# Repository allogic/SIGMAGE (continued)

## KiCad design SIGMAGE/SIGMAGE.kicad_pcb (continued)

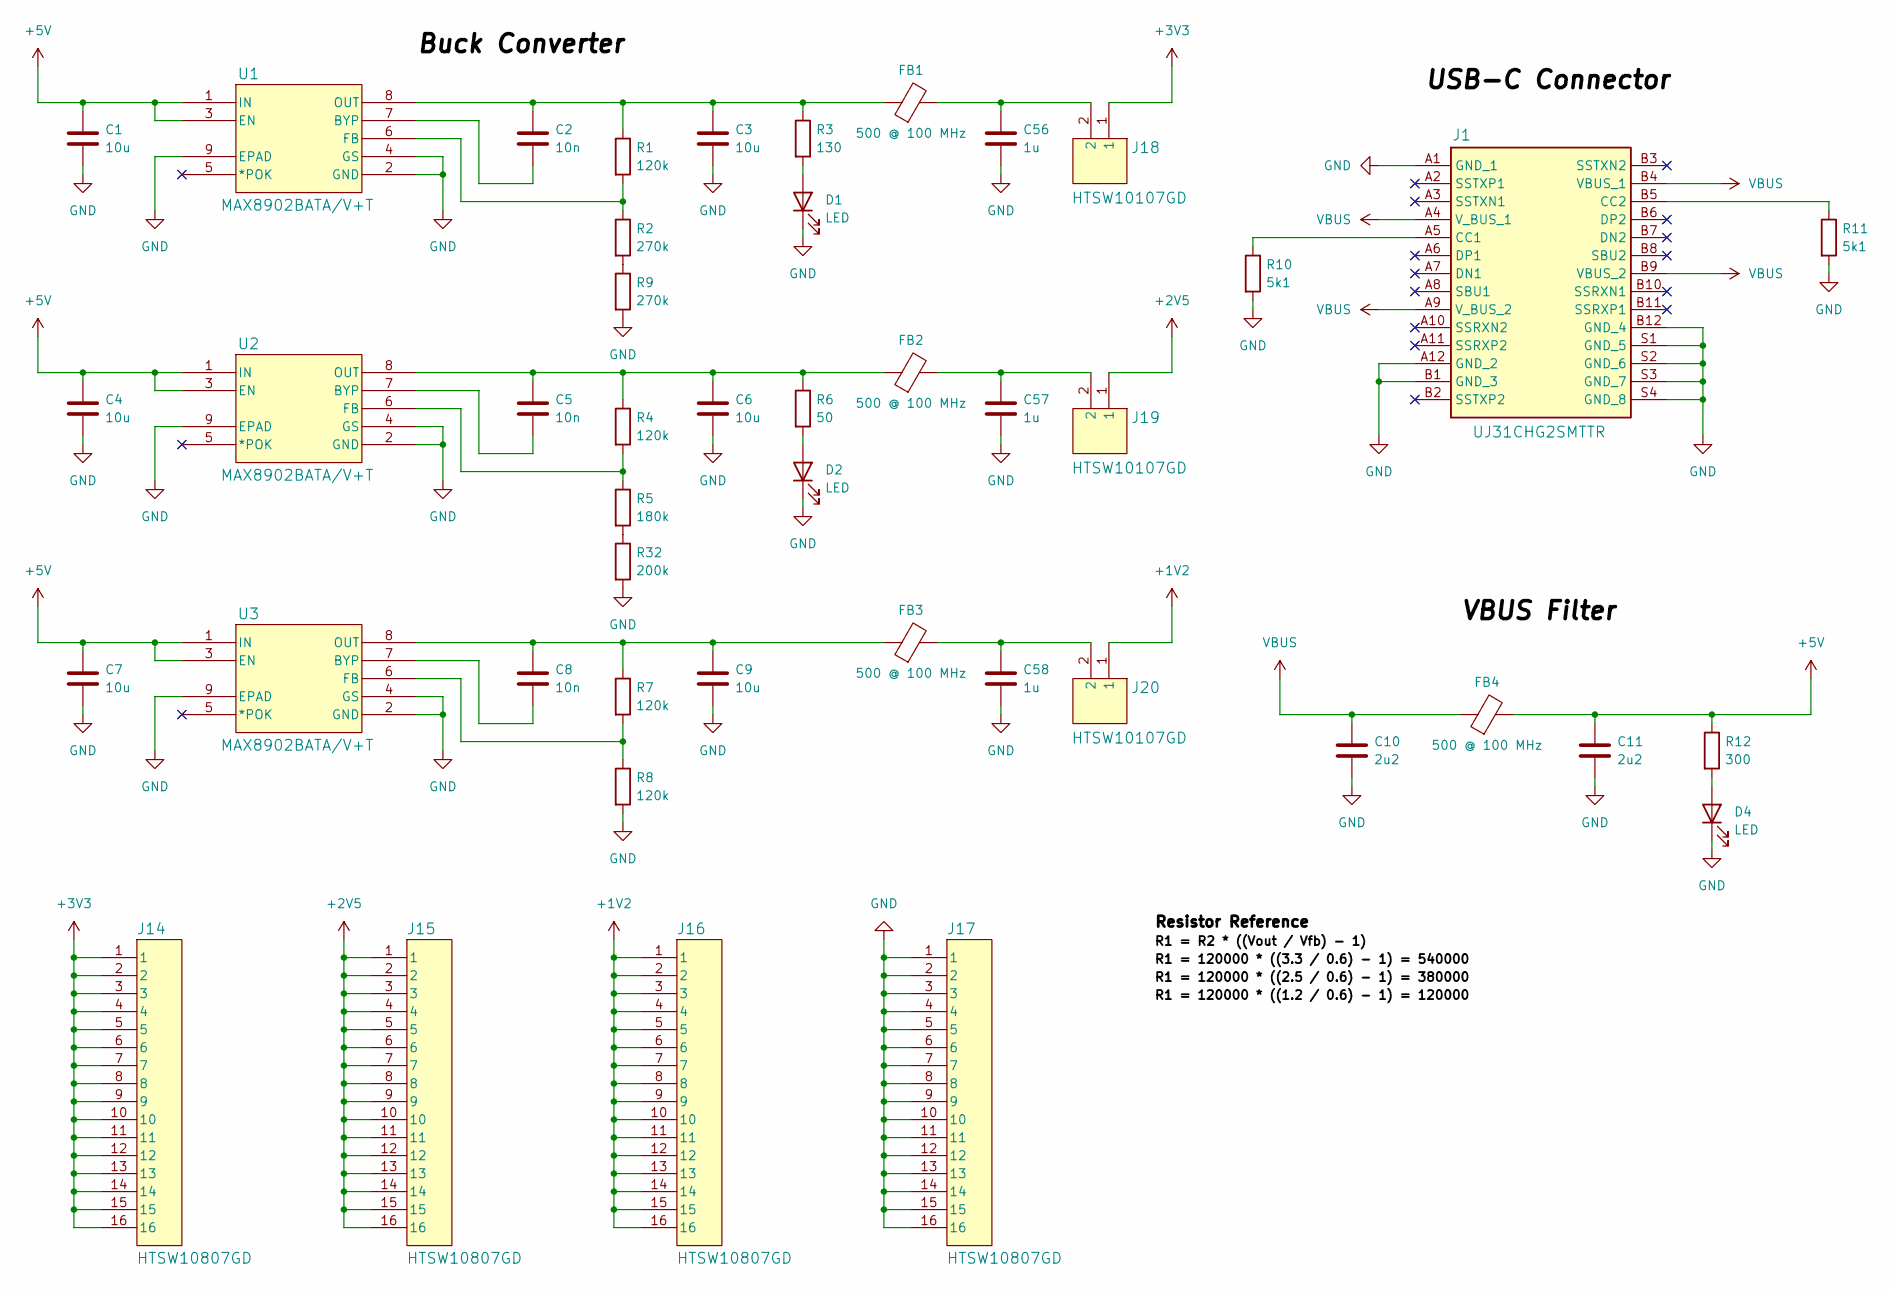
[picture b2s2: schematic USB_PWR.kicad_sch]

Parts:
C1, C3, C4, C6, C7, C9: 10u; C_0603_1608Metric
C2, C5, C8: 10n; C_0603_1608Metric
C10, C11: 2u2; C_0603_1608Metric
C56, C57, C58: 1u; C_0603_1608Metric
D1, D2, D4: LED; LED_0603_1608Metric
FB1, FB2, FB3, FB4: 500 @ 100 MHz; C_0603_1608Metric
J1: UJ31CHG2SMTTR; Manufacturer_Part_Number UJ31-CH-G2-SMT-TR; Mouser Part Number 490-UJ31-CH-G2SMT-TR
J14, J15, J16, J17: HTSW10807GD
J18, J19, J20: HTSW10107GD
R1, R4, R7, R8: 120k; R_0603_1608Metric
R2, R9: 270k; R_0603_1608Metric
R3: 130; R_0603_1608Metric
R5: 180k; R_0603_1608Metric
R6: 50; R_0603_1608Metric
R10, R11: 5k1; R_0603_1608Metric
R12: 300; R_0603_1608Metric
R32: 200k; R_0603_1608Metric
U1, U2, U3: MAX8902BATA/V+T; MAX8902BATAVT

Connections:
GND: C1.2, C3.2, C4.2, C6.2, C7.2, C9.2, C10.2, C11.2, C56.2, C57.2, C58.2, D1.1 (K), D2.1 (K), D4.1 (K), J1.A1 (GND_1), J1.A12 (GND_2), J1.B1 (GND_3), J1.B12 (GND_4), J1.S1 (GND_5), J1.S2 (GND_6), J1.S3 (GND_7), J1.S4 (GND_8), J17.1, J17.2, J17.3, J17.4, J17.5, J17.6, J17.7, J17.8, J17.9, J17.10, J17.11, J17.12, J17.13, J17.14, J17.15, J17.16, R8.2, R9.2, R10.2, R11.2, R32.2, U1.2 (GND), U1.4 (GS), U1.9 (EPAD), U2.2 (GND), U2.4 (GS), U2.9 (EPAD), U3.2 (GND), U3.4 (GS), U3.9 (EPAD); also elsewhere on the board
unnamed: C8.1, C9.1, FB3.1, R7.1, U3.8 (OUT)
unnamed: C8.2, U3.7 (BYP)
unnamed: C56.1, FB1.2, J18.2
unnamed: C57.1, FB2.2, J19.2
unnamed: C58.1, FB3.2, J20.2
unnamed: D1.2 (A), R3.2
unnamed: D2.2 (A), R6.2
unnamed: D4.2 (A), R12.2
unnamed: J1.A5 (CC1), R10.1
unnamed: J1.B5 (CC2), R11.1
unnamed: R2.2, R9.1
unnamed: R7.2, R8.1, U3.6 (FB)
unnamed: R5.2, R32.1
unnamed: C2.2, U1.7 (BYP)
unnamed: R1.2, R2.1, U1.6 (FB)
unnamed: C2.1, C3.1, FB1.1, R1.1, R3.1, U1.8 (OUT)
unnamed: C5.2, U2.7 (BYP)
unnamed: R4.2, R5.1, U2.6 (FB)
unnamed: C5.1, C6.1, FB2.1, R4.1, R6.1, U2.8 (OUT)
VBUS: C10.1, FB4.1, J1.A4 (V_BUS_1), J1.A9 (V_BUS_2), J1.B4 (VBUS_1), J1.B9 (VBUS_2)

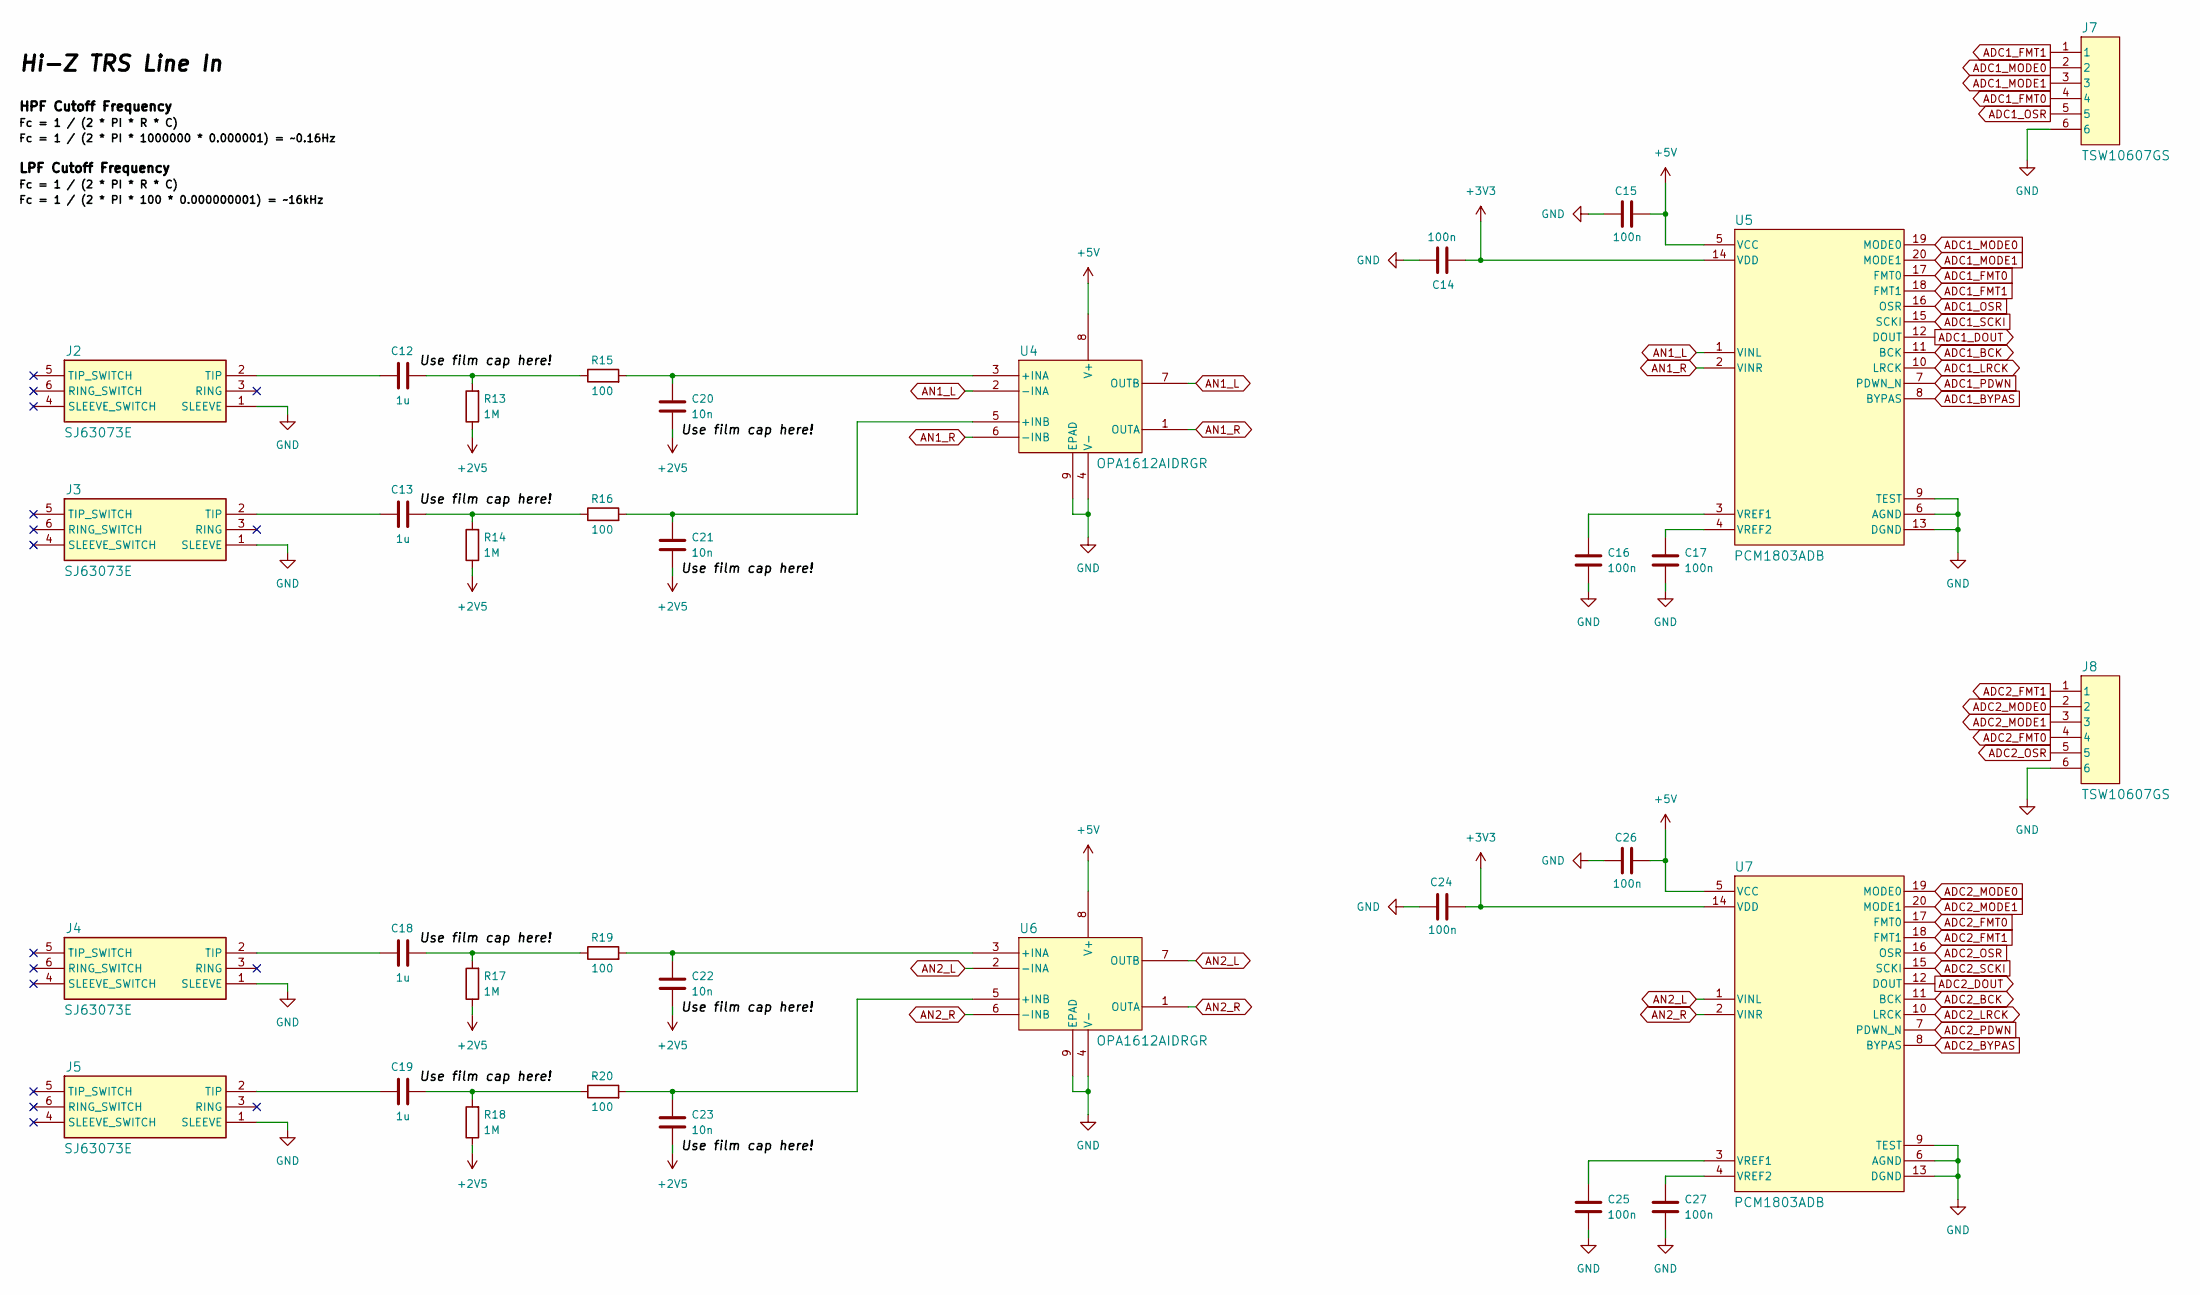
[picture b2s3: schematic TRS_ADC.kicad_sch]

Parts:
C12, C13, C18, C19: 1u; C_1206_3216Metric
C14, C15, C16, C17, C24, C25, C26, C27: 100n; C_0603_1608Metric
C20, C21, C22, C23: 10n; C_1206_3216Metric
J2, J3, J4, J5: SJ63073E; Manufacturer_Part_Number SJ-63073E; Mouser Part Number 490-SJ-63073E
J7, J8: TSW10607GS
R13, R14, R17, R18: 1M; R_0603_1608Metric
R15, R16, R19, R20: 100; R_0603_1608Metric
U4, U6: OPA1612AIDRGR
U5, U7: PCM1803ADB

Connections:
ADC1_BCK: U5.11 (BCK); also elsewhere on the board
ADC1_BYPAS: U5.8 (BYPAS); also elsewhere on the board
ADC1_DOUT: U5.12 (DOUT); also elsewhere on the board
ADC1_FMT0: J7.4, U5.17 (FMT0)
ADC1_FMT1: J7.1, U5.18 (FMT1)
ADC1_LRCK: U5.10 (LRCK); also elsewhere on the board
ADC1_MODE0: J7.2, U5.19 (MODE0)
ADC1_MODE1: J7.3, U5.20 (MODE1)
ADC1_OSR: J7.5, U5.16 (OSR)
ADC1_PDWN: U5.7 (PDWN_N); also elsewhere on the board
ADC1_SCKI: U5.15 (SCKI); also elsewhere on the board
ADC2_BCK: U7.11 (BCK); also elsewhere on the board
ADC2_BYPAS: U7.8 (BYPAS); also elsewhere on the board
ADC2_DOUT: U7.12 (DOUT); also elsewhere on the board
ADC2_FMT0: J8.4, U7.17 (FMT0)
ADC2_FMT1: J8.1, U7.18 (FMT1)
ADC2_LRCK: U7.10 (LRCK); also elsewhere on the board
ADC2_MODE0: J8.2, U7.19 (MODE0)
ADC2_MODE1: J8.3, U7.20 (MODE1)
ADC2_OSR: J8.5, U7.16 (OSR)
ADC2_PDWN: U7.7 (PDWN_N); also elsewhere on the board
ADC2_SCKI: U7.15 (SCKI); also elsewhere on the board
AN1_L: U4.2 (-INA), U4.7 (OUTB), U5.1 (VINL)
AN1_R: U4.1 (OUTA), U4.6 (-INB), U5.2 (VINR)
AN2_L: U6.2 (-INA), U6.7 (OUTB), U7.1 (VINL)
AN2_R: U6.1 (OUTA), U6.6 (-INB), U7.2 (VINR)
GND: C14.2, C15.1, C16.2, C17.2, C24.1, C25.2, C26.1, C27.2, J2.1 (SLEEVE), J3.1 (SLEEVE), J4.1 (SLEEVE), J5.1 (SLEEVE), J7.6, J8.6, U4.4 (V-), U4.9 (EPAD), U5.6 (AGND), U5.9 (TEST), U5.13 (DGND), U6.4 (V-), U6.9 (EPAD), U7.6 (AGND), U7.9 (TEST), U7.13 (DGND); also elsewhere on the board
unnamed: C12.2, R13.2, R15.1
unnamed: C13.2, R14.2, R16.1
unnamed: C18.2, R17.2, R19.1
unnamed: C19.2, R18.2, R20.1
unnamed: C12.1, J2.2 (TIP)
unnamed: C13.1, J3.2 (TIP)
unnamed: C18.1, J4.2 (TIP)
unnamed: C19.1, J5.2 (TIP)
unnamed: C20.1, R15.2, U4.3 (+INA)
unnamed: C21.1, R16.2, U4.5 (+INB)
unnamed: C16.1, U5.3 (VREF1)
unnamed: C17.1, U5.4 (VREF2)
unnamed: C22.1, R19.2, U6.3 (+INA)
unnamed: C23.1, R20.2, U6.5 (+INB)
unnamed: C25.1, U7.3 (VREF1)
unnamed: C27.1, U7.4 (VREF2)

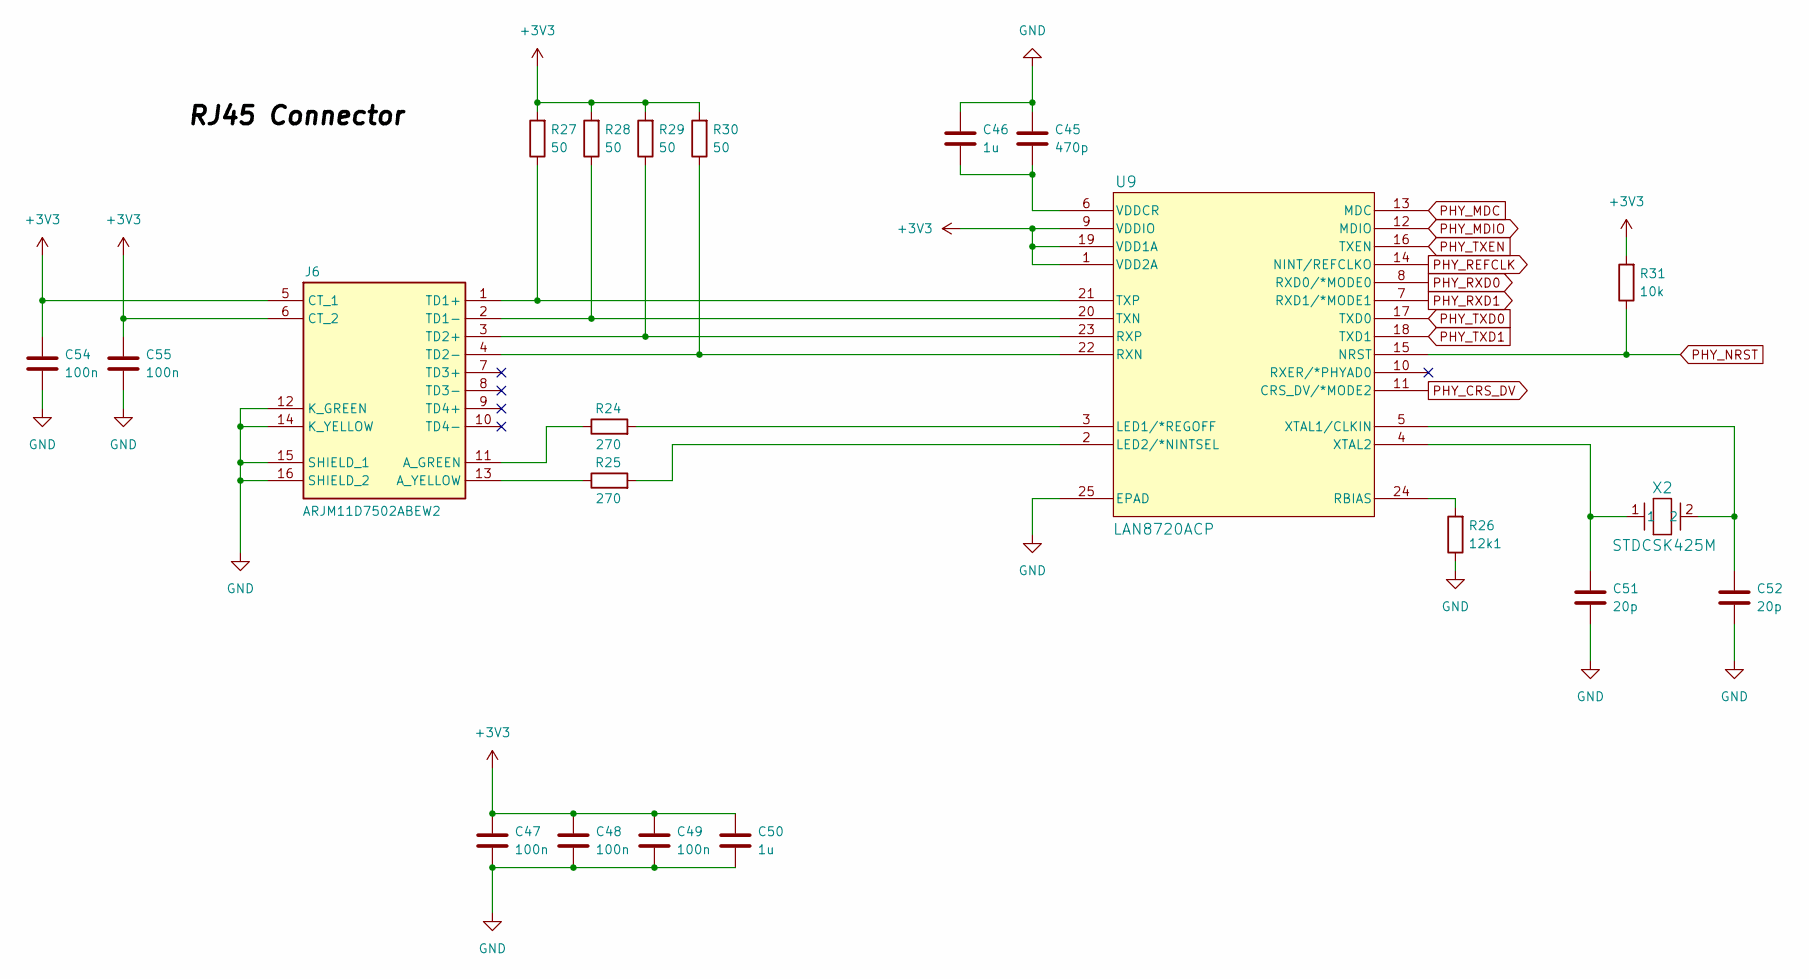
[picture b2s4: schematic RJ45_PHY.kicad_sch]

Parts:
C45: 470p; C_0603_1608Metric
C46, C50: 1u; C_0603_1608Metric
C47, C48, C49, C54, C55: 100n; C_0603_1608Metric
C51, C52: 20p; C_0603_1608Metric
J6: ARJM11D7502ABEW2; Manufacturer_Part_Number ARJM11D7-502-AB-EW2; Mouser Part Number 815-RJM11D7502ABEW2
R24, R25: 270; R_0603_1608Metric
R26: 12k1; R_0603_1608Metric
R27, R28, R29, R30: 50; R_0603_1608Metric
R31: 10k; R_0603_1608Metric
U9: LAN8720ACP
X2: STDCSK425M

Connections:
GND: C45.1, C46.1, C47.2, C48.2, C49.2, C50.2, C51.2, C52.2, C54.2, C55.2, J6.12 (K_GREEN), J6.14 (K_YELLOW), J6.15 (SHIELD_1), J6.16 (SHIELD_2), R26.1, U9.25 (EPAD); also elsewhere on the board
unnamed: J6.11 (A_GREEN), R24.1
unnamed: J6.13 (A_YELLOW), R25.1
unnamed: J6.1 (TD1+), R27.1, U9.21 (TXP)
unnamed: J6.2 (TD1-), R28.1, U9.20 (TXN)
unnamed: J6.3 (TD2+), R29.1, U9.23 (RXP)
unnamed: J6.4 (TD2-), R30.1, U9.22 (RXN)
unnamed: R24.2, U9.3 (LED1/*REGOFF)
unnamed: R25.2, U9.2 (LED2/*NINTSEL)
unnamed: R26.2, U9.24 (RBIAS)
unnamed: C45.2, C46.2, U9.6 (VDDCR)
unnamed: C52.1, U9.5 (XTAL1/CLKIN), X2.2
unnamed: C51.1, U9.4 (XTAL2), X2.1
PHY_CRS_DV: U9.11 (CRS_DV/*MODE2); also elsewhere on the board
PHY_MDC: U9.13 (MDC); also elsewhere on the board
PHY_MDIO: U9.12 (MDIO); also elsewhere on the board
PHY_NRST: R31.1, U9.15 (NRST); also elsewhere on the board
PHY_REFCLK: U9.14 (NINT/REFCLKO); also elsewhere on the board
PHY_RXD0: U9.8 (RXD0/*MODE0); also elsewhere on the board
PHY_RXD1: U9.7 (RXD1/*MODE1); also elsewhere on the board
PHY_TXD0: U9.17 (TXD0); also elsewhere on the board
PHY_TXD1: U9.18 (TXD1); also elsewhere on the board
PHY_TXEN: U9.16 (TXEN); also elsewhere on the board

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
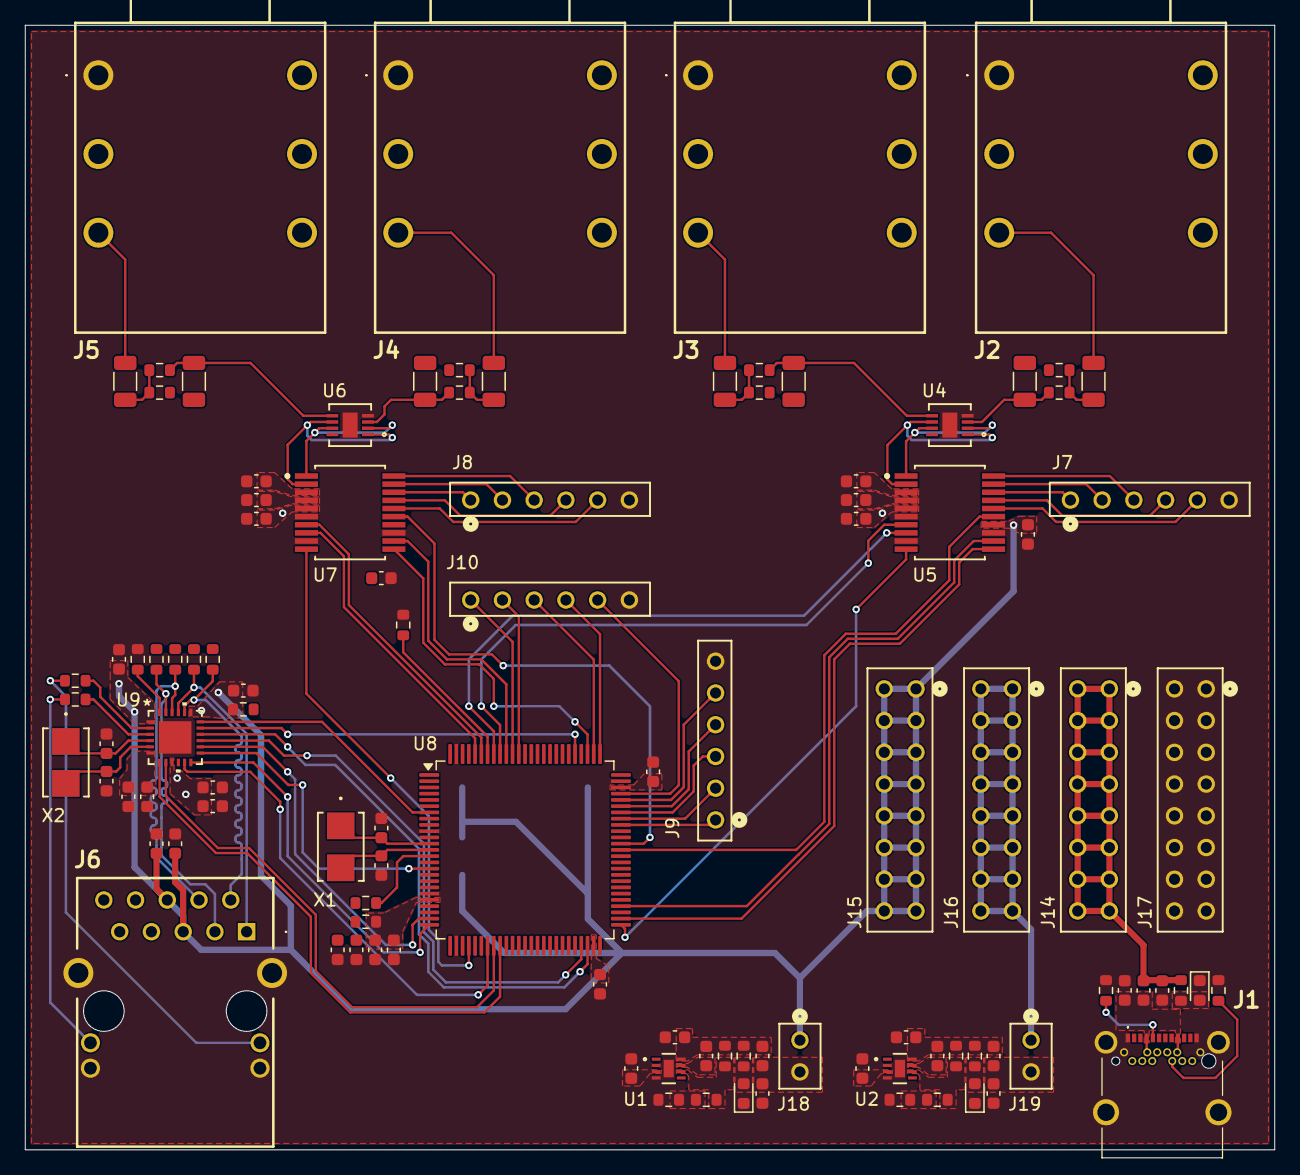
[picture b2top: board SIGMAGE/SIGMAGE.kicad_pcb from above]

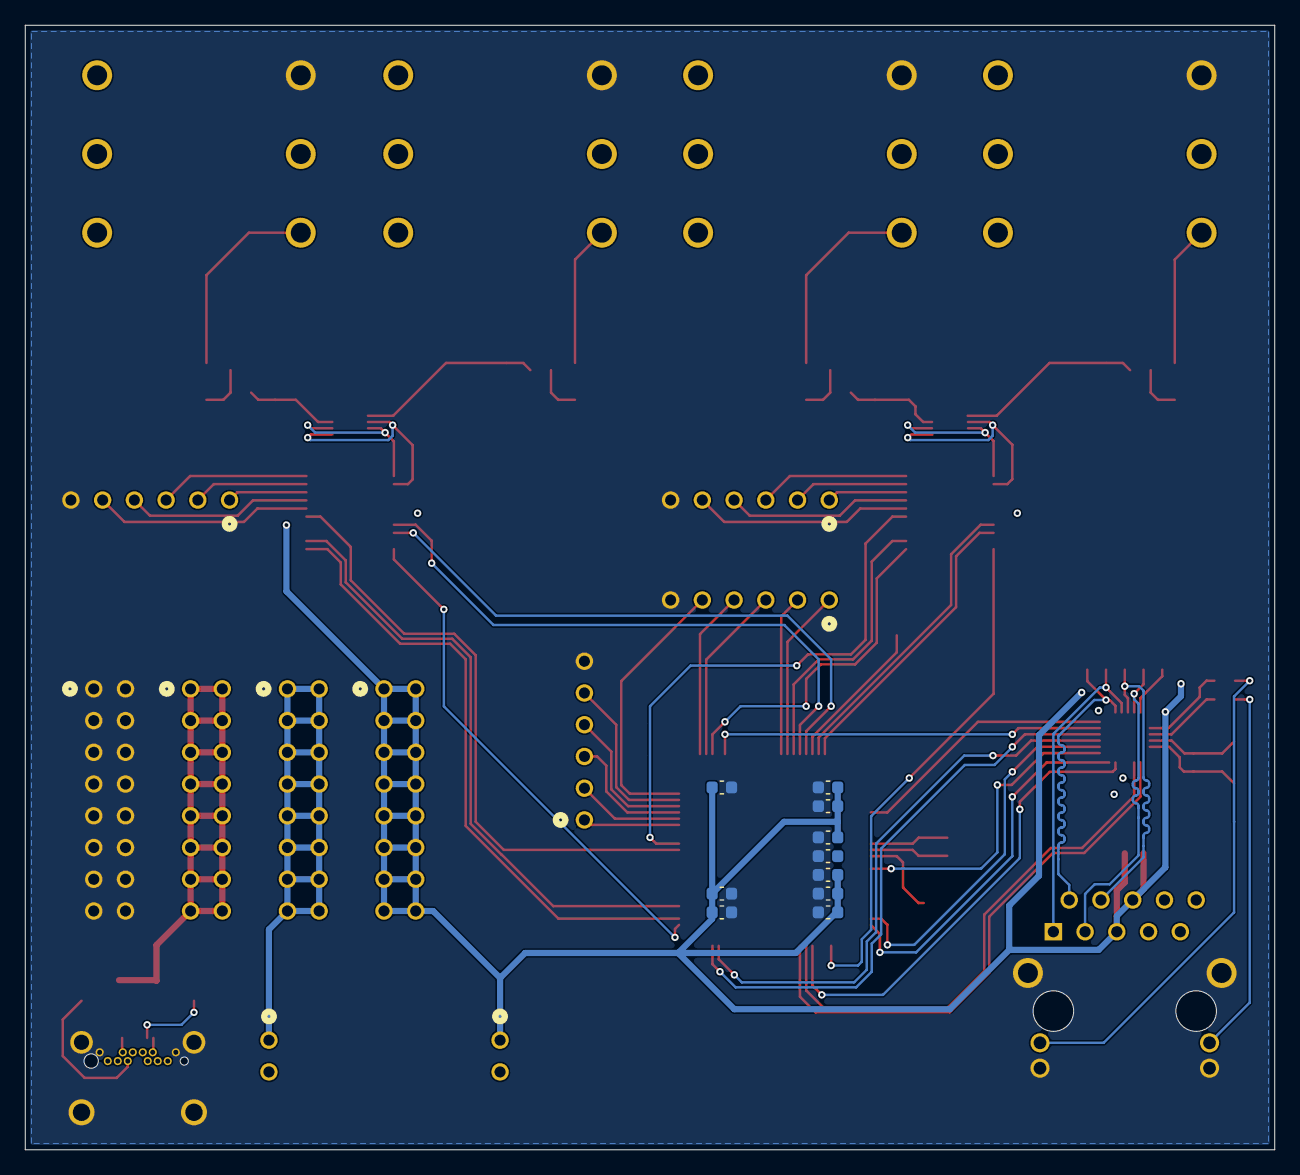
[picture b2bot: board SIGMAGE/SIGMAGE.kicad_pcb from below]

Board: 2 copper layers, 100.0 x 90.0 mm, 116 parts (10 on the bottom side), 101 nets.

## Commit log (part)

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2026-03-27 Added Hi-Z audio inputs
2026-03-28 Added RJ45/PHY and MCU
2026-03-29 Finished schematic
2026-03-30 Added PCB layout and started routing
2026-03-31 Almost finished routing
2026-04-01 Finished PCB
2026-04-01 Passed DRC check
2026-04-01 Added JLCPCB compliant gerber files
2026-04-07 Final touches, PCB layout is still horrible, will fix in MK II
2026-04-08 Again some touches against DigiKey's assortment
2026-04-18 Makin it waaay cheaper and JLCPCB conform
2026-04-19 Some routing..
2026-04-20 Added GND planes and started power dist
2026-04-22 Almost finished tha board
2026-05-19 Adding a view DAC's
2026-05-20 More DAC changes
2026-05-24 preps for FPGA
2026-05-26 ECP5U-25F symbol
2026-05-26 some changes
2026-05-26 some changes again
2026-05-27 finished FPGA symbol
2026-05-27 some schematic adjustments
2026-05-28 added TPS62130RGTT and added digital/analog converter
2026-05-31 some USB interface
2026-06-01 more USB stuff
2026-06-02 some FPGA stuff
2026-06-08 added SPI flash
2026-06-12 major changes
2026-06-15 finishing up
2026-06-16 almost done
2026-06-17 before sync sheets
2026-06-17 wrong mezzanine
2026-06-18 added board interconnect headers
2026-06-18 something
2026-06-18 basic layout
2026-06-21 uga uga
2026-06-22 almost done with tha top part
2026-06-23 stuff
2026-06-24 some foo
2026-06-24 more foo
2026-06-24 improvements
2026-06-25 foo bar
2026-06-26 more routing
2026-06-29 shitty power traces part one
2026-06-30 some more power stuff
